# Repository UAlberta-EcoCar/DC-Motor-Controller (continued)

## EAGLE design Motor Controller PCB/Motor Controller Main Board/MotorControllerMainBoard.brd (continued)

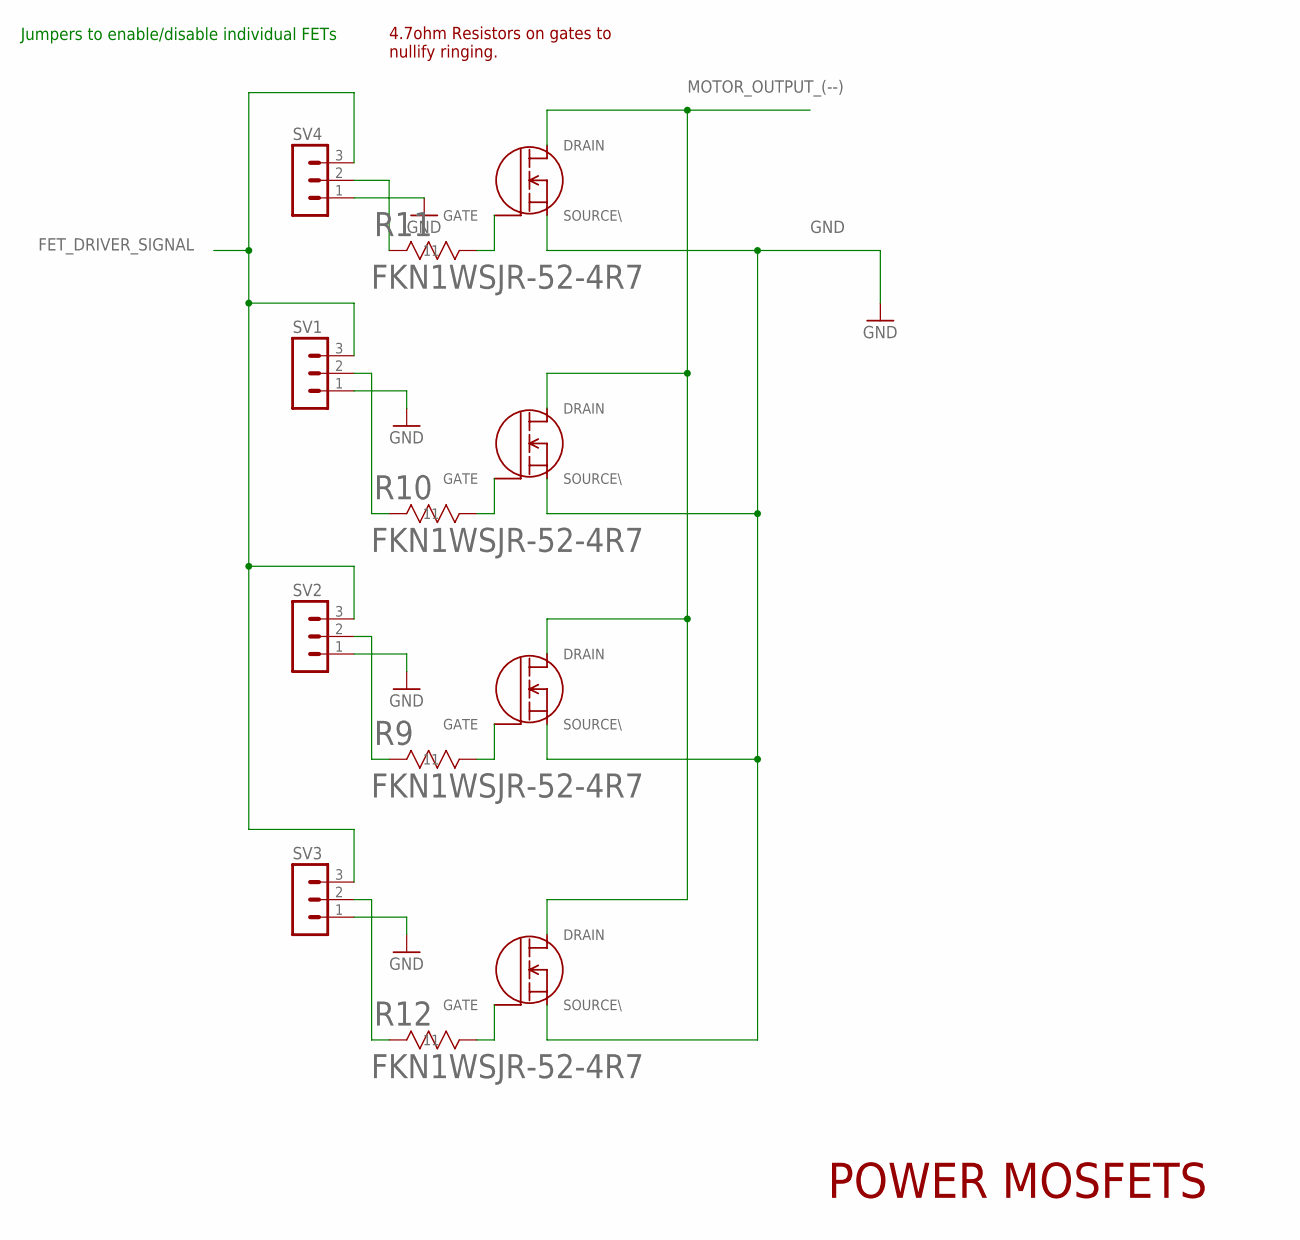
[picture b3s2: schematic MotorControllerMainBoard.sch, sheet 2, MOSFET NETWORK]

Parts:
R9, R10, R11, R12: FKN1WSJR-52-4R7; YAG_FKN50
SV1, SV2, SV3, SV4: MA03-1
U$1, U$2, U$3, U$4: NTMFS5C426NT1G; DNF5

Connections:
FET_DRIVER_SIGNAL: SV1.3, SV2.3, SV3.3, SV4.3; also elsewhere on the board
GND: SV1.1, SV2.1, SV3.1, U$1.SOURCE (SOURCE\), U$2.SOURCE (SOURCE\), U$3.SOURCE (SOURCE\), U$4.SOURCE (SOURCE\); also elsewhere on the board
MOTOR_OUTPUT_(--): U$1.DRAIN, U$2.DRAIN, U$3.DRAIN, U$4.DRAIN; also elsewhere on the board
unnamed: R10.2 (22), U$2.GATE
unnamed: R10.1 (11), SV1.2
unnamed: R12.1 (11), SV3.2
unnamed: R11.1 (11), SV4.2
unnamed: R11.2 (22), U$1.GATE
unnamed: R9.2 (22), U$3.GATE
unnamed: R12.2 (22), U$4.GATE
unnamed: R9.1 (11), SV2.2

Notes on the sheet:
POWER MOSFETS
Jumpers to enable/disable individual FETs
4.7ohm Resistors on gates to nullify ringing.

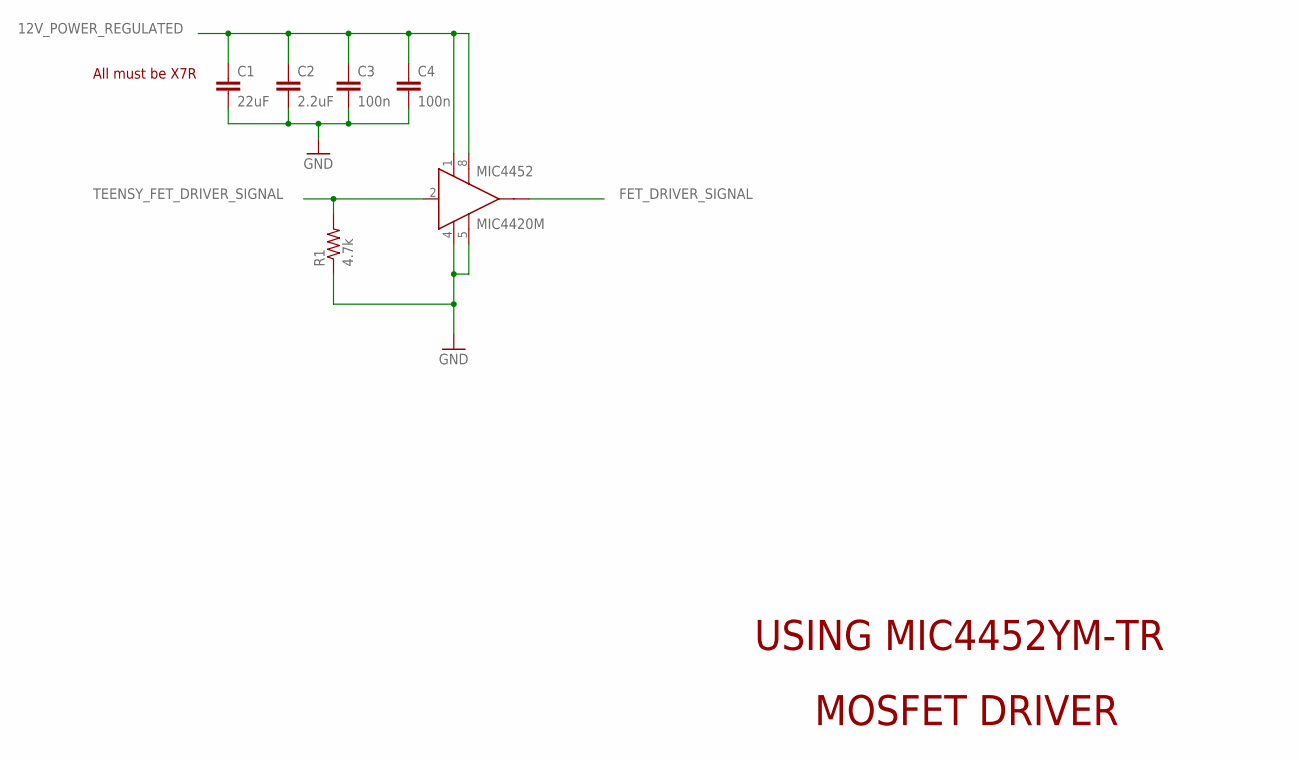
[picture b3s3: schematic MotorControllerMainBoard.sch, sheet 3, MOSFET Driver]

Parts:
C1: 22uF; C1206
C2: 2.2uF; C0805
C3, C4: 100n; C0603
MIC4452: MIC4420M; SO-08
R1: 4.7k; R0805

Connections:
12V_POWER_REGULATED: C1.1, C2.1, C3.1, C4.1, MIC4452.1 (VS), MIC4452.8 (VS1); also elsewhere on the board
FET_DRIVER_SIGNAL: MIC4452.6 (OUT); also elsewhere on the board
GND: C1.2, C2.2, C3.2, C4.2, MIC4452.4 (GND), MIC4452.5 (GND1), R1.1; also elsewhere on the board
TEENSY_FET_DRIVER_SIGNAL: MIC4452.2 (IN), R1.2; also elsewhere on the board

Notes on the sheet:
MOSFET DRIVER
USING MIC4452YM-TR
All must be X7R

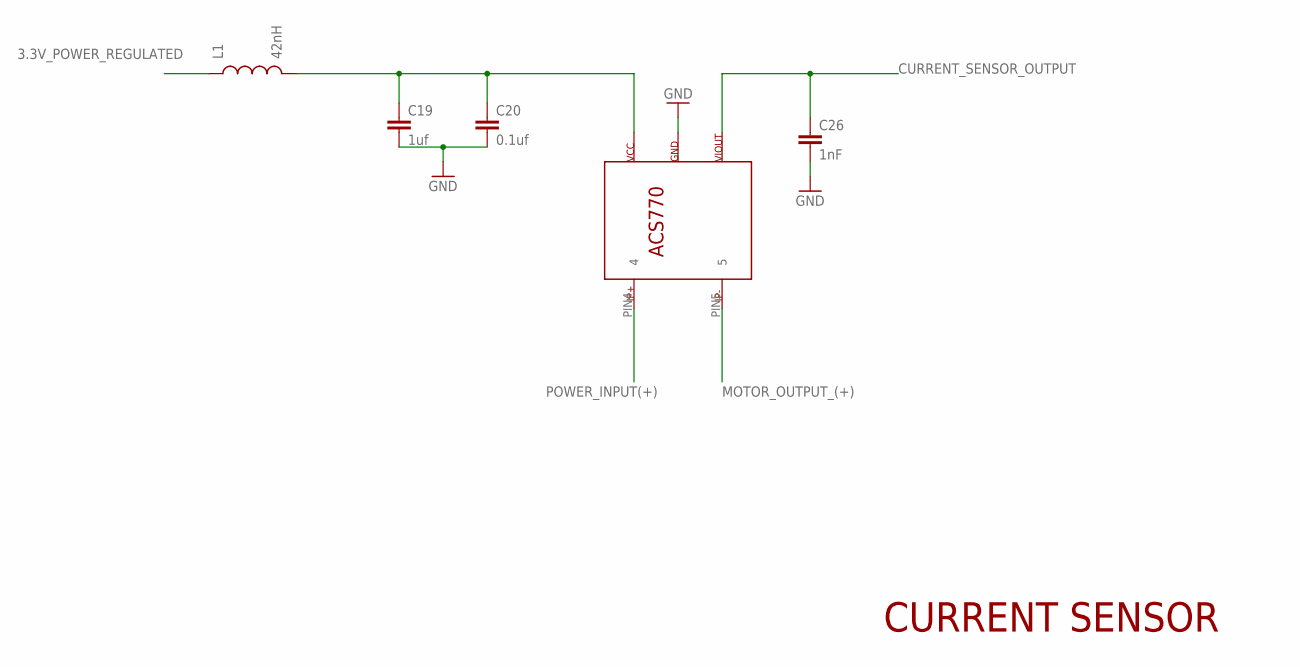
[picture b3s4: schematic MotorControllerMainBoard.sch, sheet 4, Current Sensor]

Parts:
C19: 1uf; C0805
C20: 0.1uf; C0805
C26: 1nF; C0805
L1: 42nH; 0805
U$9: ACS770LCB_CURRENTSENSOR

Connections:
3.3V_POWER_REGULATED: L1.1; also elsewhere on the board
CURRENT_SENSOR_OUTPUT: C26.1, U$9.PIN3 (3); also elsewhere on the board
GND: C19.2, C20.2, C26.2, U$9.PIN2 (2); also elsewhere on the board
MOTOR_OUTPUT_(+): U$9.PIN5 (5); also elsewhere on the board
unnamed: C19.1, C20.1, L1.2, U$9.PIN1 (1)
POWER_INPUT(+): U$9.PIN4 (4)

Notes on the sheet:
CURRENT SENSOR

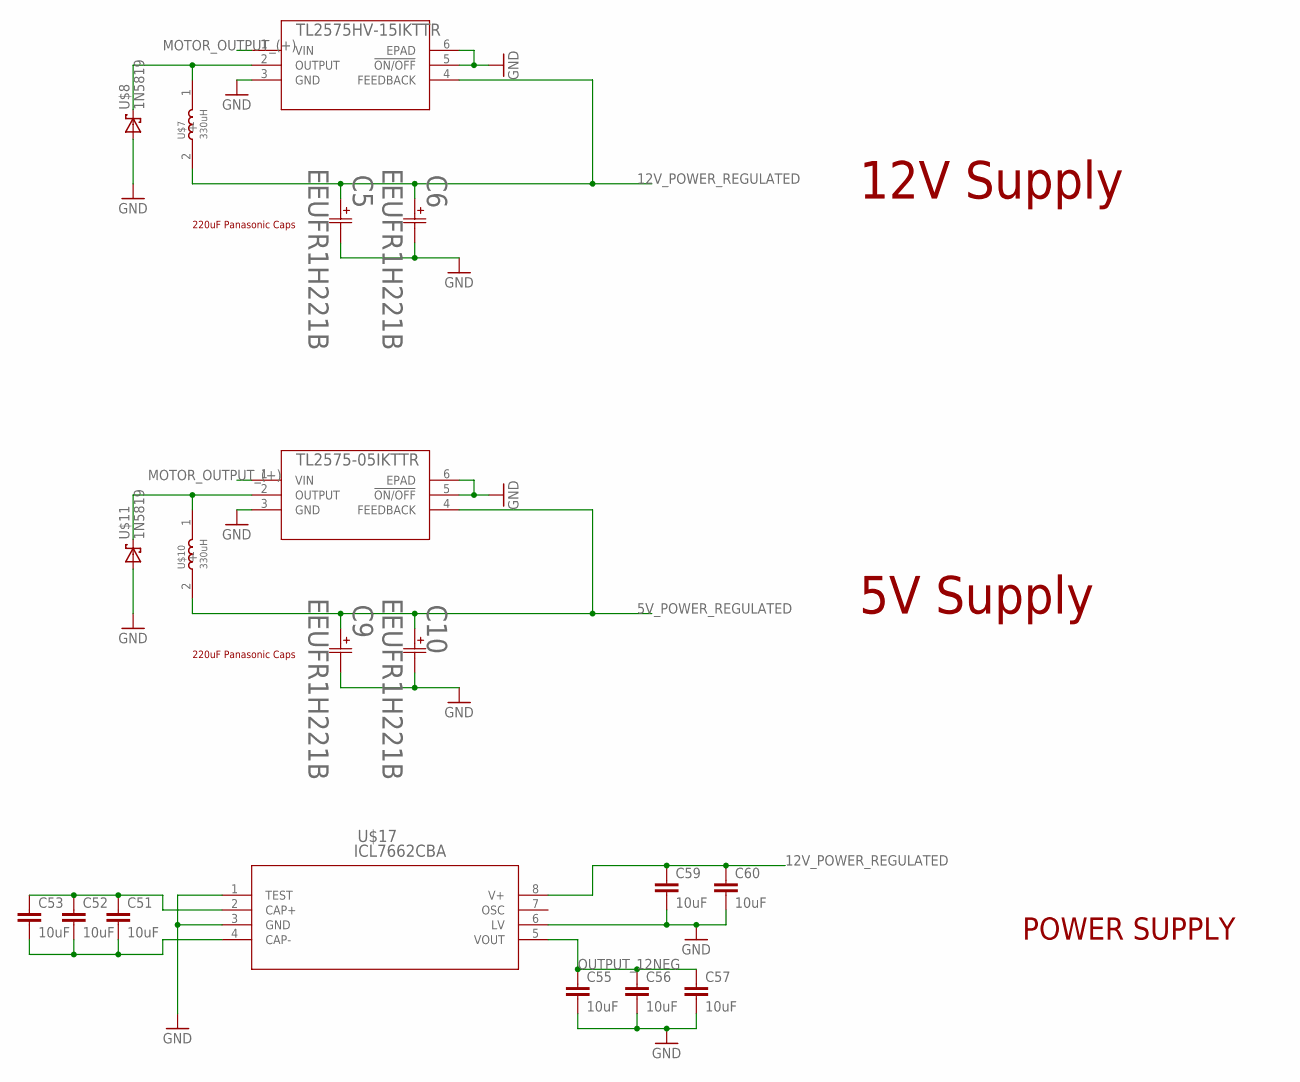
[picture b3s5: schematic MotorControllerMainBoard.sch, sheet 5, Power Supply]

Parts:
C5, C6, C9, C10: EEUFR1H221B; CAP_PAN_10X16
C51, C52, C53, C55, C56, C57, C59, C60: 10uF; C0805
U$6: TL2575HV-15IKTTR; KTT5_6P22X6P86
U$7, U$10: 330uH; INDUCTOR_SMD_FOOTPRINT
U$8, U$11: 1N5819; SOD3715X135N
U$13: TL2575-05IKTTR; KTT5_6P22X6P86
U$17: ICL7662CBA; SO08

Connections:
5V_POWER_REGULATED: C9.1 (11), C10.1 (11), U$10.2 (-), U$13.4 (FEEDBACK); also elsewhere on the board
12V_POWER_REGULATED: C5.1 (11), C6.1 (11), C59.1, C60.1, U$6.4 (FEEDBACK), U$7.2 (-), U$17.8 (V+); also elsewhere on the board
GND: C5.2 (22), C6.2 (22), C9.2 (22), C10.2 (22), C55.2, C56.2, C57.2, C59.2, C60.2, U$6.3 (GND), U$6.5 (!ON/OFF), U$6.6 (EPAD), U$8.A, U$11.A, U$13.3 (GND), U$13.5 (!ON/OFF), U$13.6 (EPAD), U$17.1 (TEST), U$17.3 (GND), U$17.6 (LV); also elsewhere on the board
MOTOR_OUTPUT_(+): U$6.1 (VIN), U$13.1 (VIN); also elsewhere on the board
unnamed: U$6.2 (OUTPUT), U$7.1 (+), U$8.C (K)
unnamed: U$10.1 (+), U$11.C (K), U$13.2 (OUTPUT)
unnamed: C51.1, C52.1, C53.1, U$17.2 (CAP+)
unnamed: C51.2, C52.2, C53.2, U$17.4 (CAP-)
OUTPUT_12NEG: C55.1, C56.1, C57.1, U$17.5 (VOUT); also elsewhere on the board

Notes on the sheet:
POWER SUPPLY
12V Supply
5V Supply
220uF Panasonic Caps

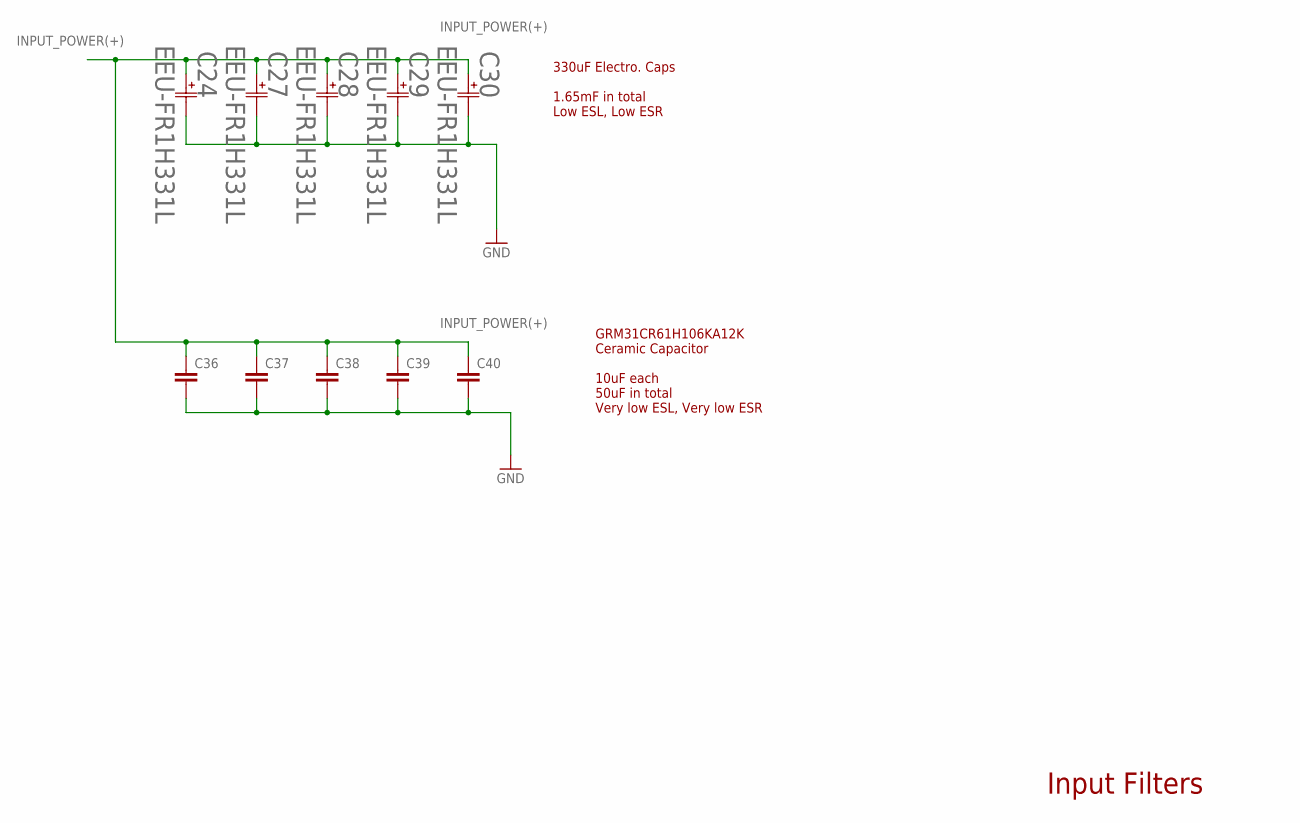
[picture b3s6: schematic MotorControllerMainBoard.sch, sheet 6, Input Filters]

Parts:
C24, C27, C28, C29, C30: EEU-FR1H331L; CAP_EEUFC_10X25
C36, C37, C38, C39, C40: C-EUC1206; C1206

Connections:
GND: C24.2 (22), C27.2 (22), C28.2 (22), C29.2 (22), C30.2 (22), C36.2, C37.2, C38.2, C39.2, C40.2; also elsewhere on the board
INPUT_POWER(+): C24.1 (11), C27.1 (11), C28.1 (11), C29.1 (11), C30.1 (11), C36.1, C37.1, C38.1, C39.1, C40.1; also elsewhere on the board

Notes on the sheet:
Input Filters
GRM31CR61H106KA12K Ceramic Capacitor 10uF each 50uF in total Very low ESL, Very low ESR
330uF Electro. Caps 1.65mF in total Low ESL, Low ESR

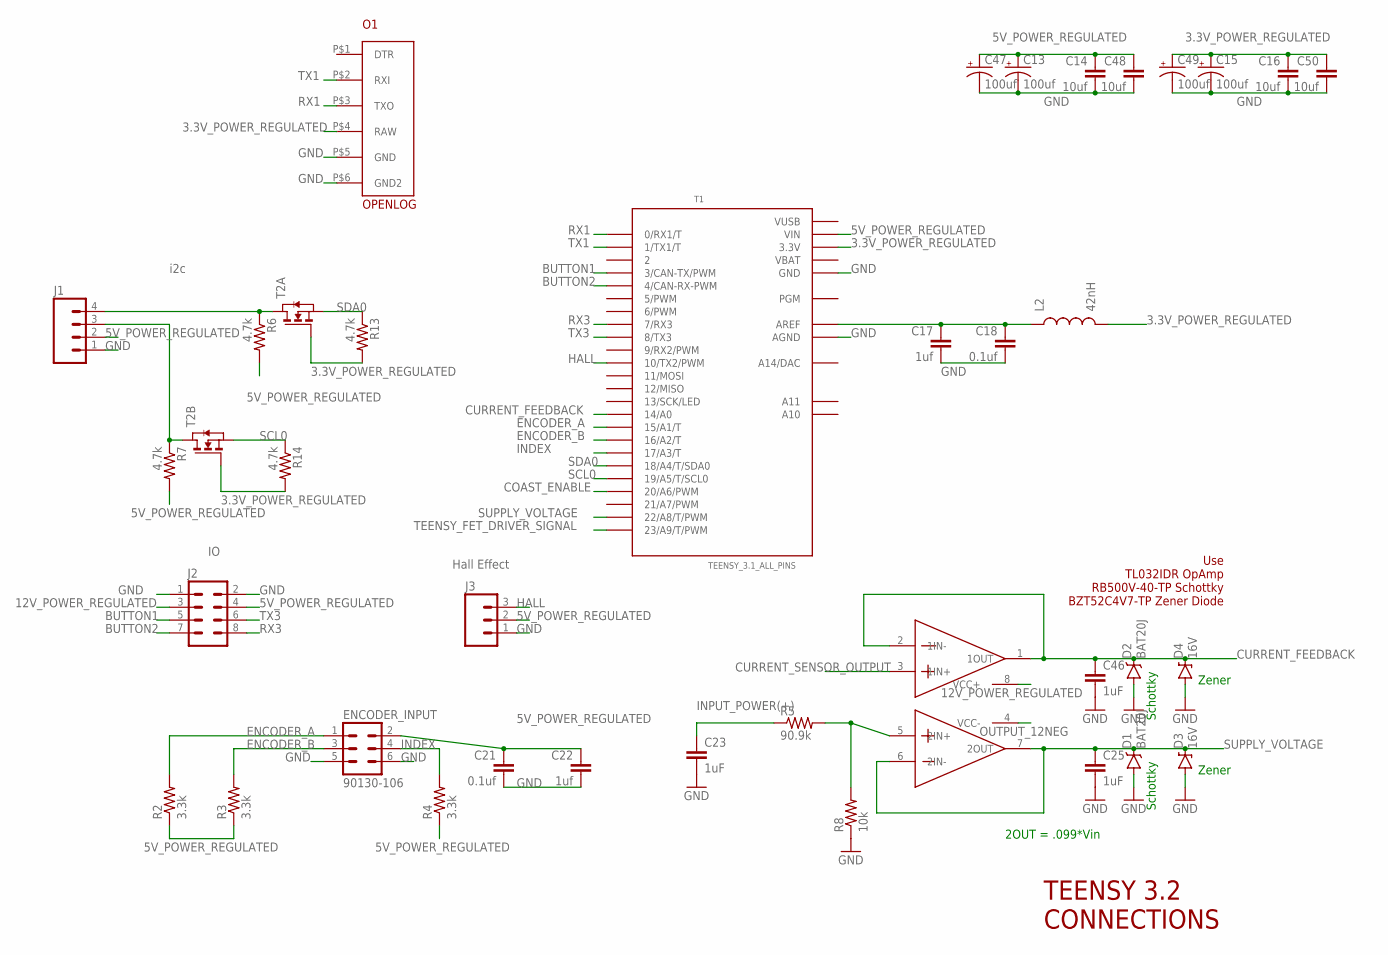
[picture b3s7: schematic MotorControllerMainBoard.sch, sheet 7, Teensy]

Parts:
AD8512ARZ: TL072CDT; D8
C13, C15, C47, C49: 100uf; PANASONIC_C
C14, C16, C48, C50: 10uf; C0805
C17, C22: 1uf; C0805
C18, C21: 0.1uf; C0805
C23, C25, C46: 1uF; C0805
D1, D2: BAT20J; SOD-323
D3, D4: 16V; SOD-123
ENCODER_INPUT: 90130-106; 90130-1?06
J1: M04PTH; 1X04
J2: M04X2; 2X4
J3: M03PTH; 1X03
L2: 42nH; 0805
O1: OPENLOG
R2, R3, R4: 3.3k; R0805
R5: 90.9k; R0805
R6, R7, R13, R14: 4.7k; 0805
R8: 10k; R0805
T1: TEENSY_3.1_ALL_PINS; TEENSY3-ALL_PINS
T2: NMOS2SO8; SO8

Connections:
3.3V_POWER_REGULATED: C15.+, C16.1, C49.+, C50.1, L2.2, O1.P$4 (RAW), R13.2, R14.2, T1.3.3V, T1.3.3V1 (3.3V), T2.2 (G), T2.4 (G); also elsewhere on the board
5V_POWER_REGULATED: C13.+, C14.1, C21.1, C22.1, C47.+, C48.1, ENCODER_INPUT.2, J1.2, J2.4, J3.2, R2.1, R3.1, R4.1, R6.2, R7.2, T1.VIN; also elsewhere on the board
12V_POWER_REGULATED: AD8512ARZ.8 (VCC+), J2.3; also elsewhere on the board
BUTTON1: J2.5, T1.3 (3/CAN-TX/PWM); also elsewhere on the board
BUTTON2: J2.7, T1.4 (4/CAN-RX-PWM); also elsewhere on the board
COAST_ENABLE: T1.20/A6 (20/A6/PWM)
CURRENT_FEEDBACK: AD8512ARZ.1 (1OUT), AD8512ARZ.2 (1IN-), C46.1, D2.C, D4.C, T1.14/A0
CURRENT_SENSOR_OUTPUT: AD8512ARZ.3 (1IN+); also elsewhere on the board
ENCODER_A: ENCODER_INPUT.1, R2.2, T1.15/A1 (15/A1/T)
ENCODER_B: ENCODER_INPUT.3, R3.2, T1.16/A2 (16/A2/T)
GND: C13.-, C14.2, C15.-, C16.2, C17.2, C18.2, C21.2, C22.2, C23.2, C25.2, C46.2, C47.-, C48.2, C49.-, C50.2, D1.A, D2.A, D3.A, D4.A, ENCODER_INPUT.5, ENCODER_INPUT.6, J1.1, J2.1, J2.2, J3.1, O1.P$5 (GND), O1.P$6 (GND2), R8.1, T1.AGND, T1.GND, T1.GND1 (GND); also elsewhere on the board
HALL: J3.3, T1.10 (10/TX2/PWM)
INDEX: ENCODER_INPUT.4, R4.2, T1.17/A3 (17/A3/T)
INPUT_POWER(+): C23.1, R5.1; also elsewhere on the board
unnamed: AD8512ARZ.5 (2IN+), R5.2, R8.2
unnamed: C17.1, C18.1, L2.1, T1.AREF
unnamed: J1.3, R7.1, T2.5 (D), T2.6 (D)
unnamed: J1.4, R6.1, T2.7 (D), T2.8 (D)
OUTPUT_12NEG: AD8512ARZ.4 (VCC-); also elsewhere on the board
RX1: O1.P$3 (TXO), T1.0 (0/RX1/T)
RX3: J2.8, T1.7 (7/RX3)
SCL0: R14.1, T1.19/A5 (19/A5/T/SCL0), T2.3 (S)
SDA0: R13.1, T1.18/A4 (18/A4/T/SDA0), T2.1 (S)
SUPPLY_VOLTAGE: AD8512ARZ.6 (2IN-), AD8512ARZ.7 (2OUT), C25.1, D1.C, D3.C, T1.22/A8 (22/A8/T/PWM)
TEENSY_FET_DRIVER_SIGNAL: T1.23/A9 (23/A9/T/PWM); also elsewhere on the board
TX1: O1.P$2 (RXI), T1.1 (1/TX1/T)
TX3: J2.6, T1.8 (8/TX3)
VBAT: T1.VBAT
VUSB: T1.VUSB

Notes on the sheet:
TEENSY 3.2 CONNECTIONS
2OUT = .099*Vin
Use TL032IDR OpAmp RB500V-40-TP Schottky BZT52C4V7-TP Zener Diode
Zener
Schottky
i2c
Hall Effect

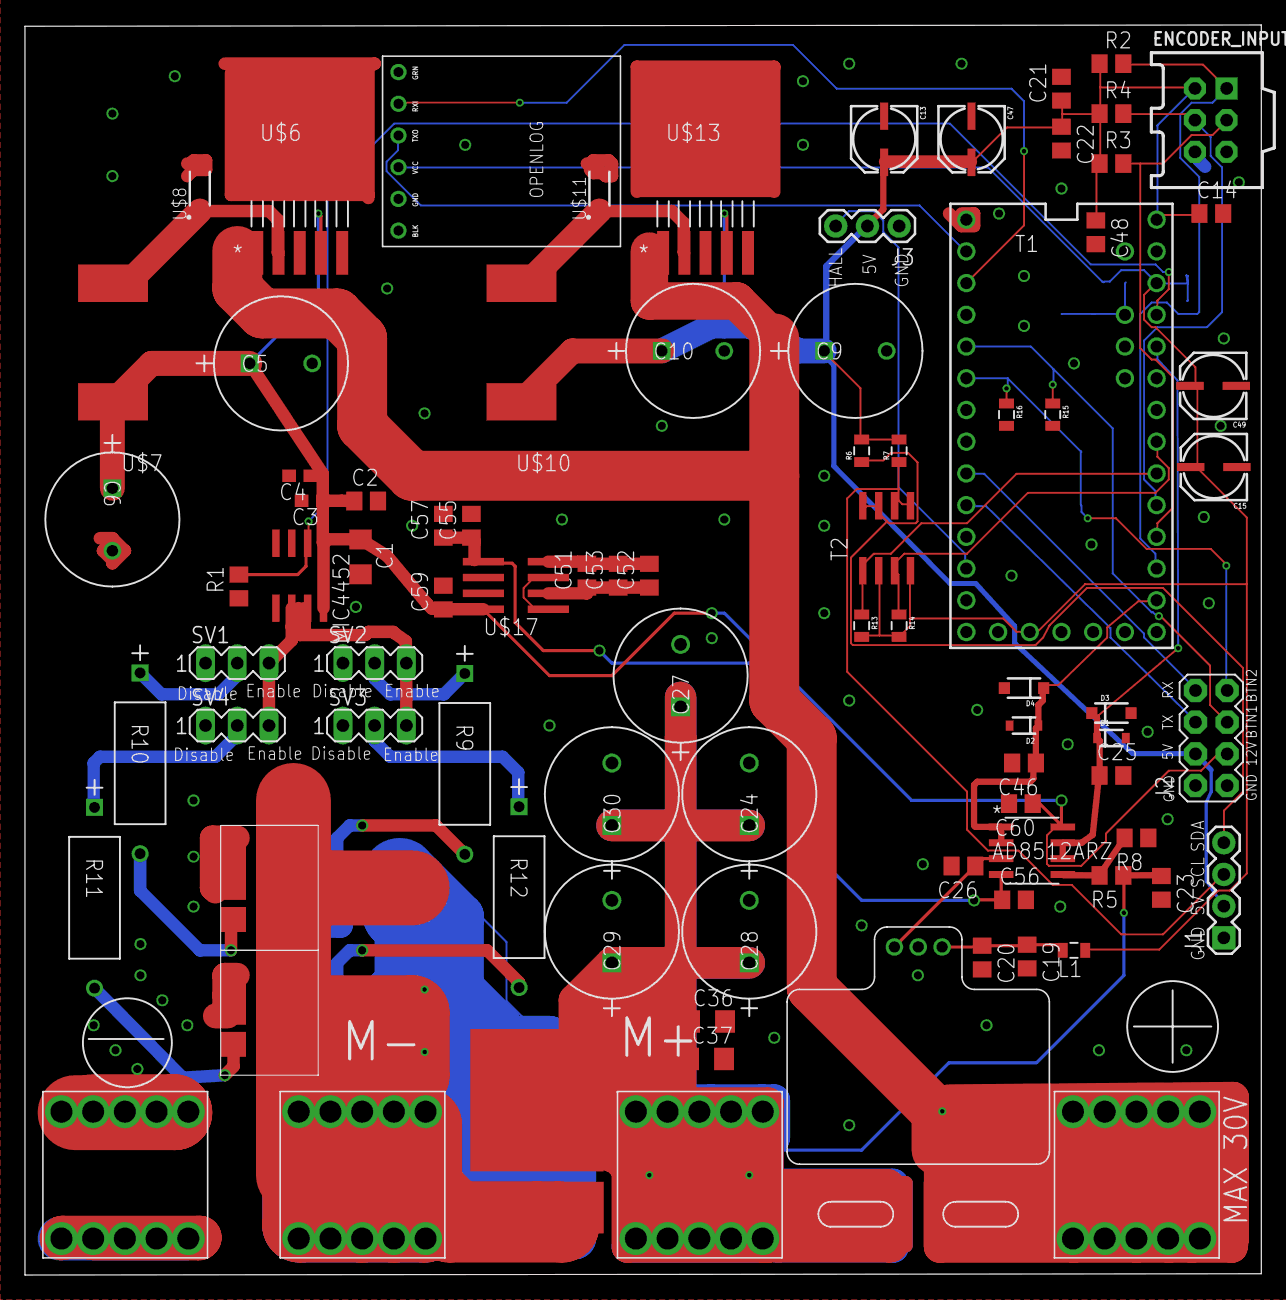
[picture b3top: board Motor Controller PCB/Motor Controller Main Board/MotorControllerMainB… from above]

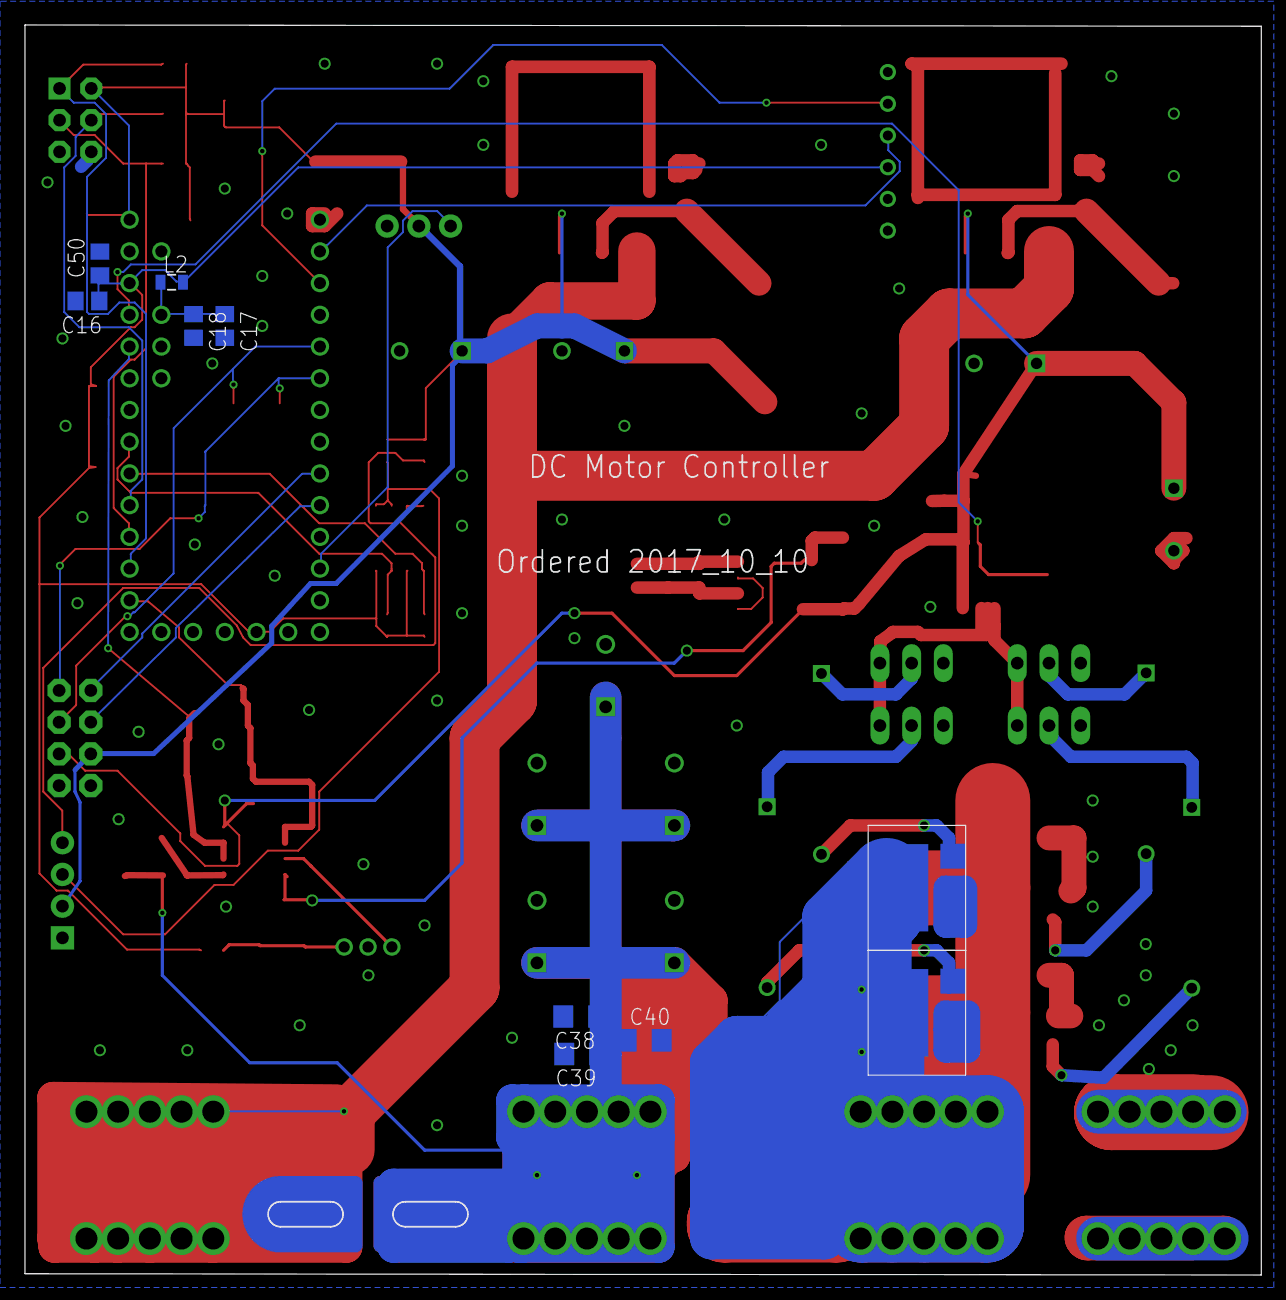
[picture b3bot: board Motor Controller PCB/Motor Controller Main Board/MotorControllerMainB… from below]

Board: 2 copper layers, 98.9 x 100.0 mm, 96 parts (10 on the bottom side), 42 nets.

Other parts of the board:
R15, R16: 10k; 0805

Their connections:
BUTTON1: R15.1; also elsewhere on the board
BUTTON2: R16.1; also elsewhere on the board
GND: R15.2, R16.2; also elsewhere on the board

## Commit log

2017-05-29 Started a general folder layout
    Gotta keep organized !
2017-05-29 Initialized platformIO for atom
2017-06-02 Setup the Topology
    Fill out the boxes! Make use of sheets to keep it simple and tidy.
2017-06-02 Created PID class
    Started working on the PID class
2017-06-03 Added onto PID class
    Continued work on the PID class
2017-06-03 Tested it with a physical setup
    Tested the code with a physical setup, a teensy and a small DC motor. It
    works.
2017-06-06 Added Some Overflow Protections
    Added protections so signed 32 bit integers do not overflow.
2017-06-08 Worked on Overflow Protection
2017-06-09 Added to desision spreadsheet
2017-06-15 Started Simulation
    -Needs some tweaks
    -Needs actual values put into the .m file.
2017-06-15 Added Mosfet Network Block
    Selected a nMOS to use and added it to the eagle schematic.
    Didnt have an eagle part, so I made. I made the pads extra large so we
    can get to it with an iron.
2017-06-16 Added MOSFET Driver
2017-06-19 Replaced code that was lost
2017-06-19 Added Teensy Symbol
2017-06-20 Added Flyback Diode
    Should able to mount the active diode and the schotky diode onto the pad
    layout. Dispite them having different packages.
2017-06-22 Added libraries for the 5V and 15V regulator
2017-06-22 Added datasheet for the 15V and 5V regulator
    They have the same data sheet;
    The TL2575.
2017-06-23 Created Inductor Symbol
2017-06-23 Added Capacitor Library
2017-07-03 Updated Eagle Library
    Updated eagle library, will work on power supply tomorrow
2017-07-04 Worked on 15V and 5V Supply
2017-07-05 Removed Trimpot on Supply
2017-07-06 Modified the mosfet network
    added headers to enable/disable individual fets
    also we're going to drive the fets with 12V instead of 15V.
2017-07-08 Added Teensy Pins
2017-07-14 Changes to current sensor LP filter
2017-07-23 Added buffers
    Choose a JFET op-amp for its ability to reject noise while having high
    input impedance.
    -Used a buffer for the output of the current sensor
    -Used a 1/10 gain buffer to read the voltage of the supply voltage
    safely.
2017-07-25 Decided to use a different op-amp
    A tad more expensive but this new op-amp selection offers little to no
    current or voltage offset voltages.
2017-07-26 Made Several Changes
2017-08-02 Added Current Sensor Part
    Still need to place it on the board (ill probably do it this weekend)
2017-08-02 Implemented the Current Sensor on the Schematic
2017-08-18 Selected a cheaper op-amp
2017-09-05 Added input filter Capacitors.
    3.4mF of input capacitance that has very low effective series resistance
    and inductance.
2017-09-11 Added Screw Terminals to Schematic
    -Added library for the screw terminal
    -Added Power terminals and Motor terminals
2017-09-12 Fixed mistake
    -I put the screw terminal for the negative port for the motor in the
    wrong spot
    -Future update needs resistors on the gates of the FETs. I figure out
    what size of resistor
2017-09-17 Still Working on It
2017-09-19 Added gate resistors
    -4.7ohm on each FET
    -Helps reduce ringing
    -Helps deal with slight difference in capacitance so that they turn on
    closer to at the same time.
2017-09-19 Paralleled power capacitors for the teensy
    -For both the 5V and 3.3V
2017-09-19 Added Negative 12V regulator for op-amps
    -Added a -12V regulator for the op-amps. Low power, simple charge pump
    that inverts the 12V regulator that already exists on the board.
2017-09-23 Preliminary Layout of Large Components
    Layout of large components, will probably move components around. Caps
    look bad and didn't align properly. We can spend time aligning them
    manually once we have the final layout.
2017-09-26 Board work and removed some caps
    -Removed 2 caps from 5V reg and 12V and -12V reg
    -Removed 5 caps from input filter and 5 ceramics
    -Larger components are in place, I started wiring the input caps.
2017-09-27 Placed all components on board
    -They just need wiring.
    -Yes I know it looks sloppy, but we need a quick prototype.
    -Final version of the board will have more thought into component
    placement
2017-09-27 Routed majority of the power components
    -Only thing left is stuff connected to teensy and other things i missed
2017-09-28 Added Header, Worked on Digital Connections
    Added 2x5 header for IO, added 1x3 header for Hall sensor. Worked on
    some digital connections, still a work in progress.
2017-09-29 Revert "Added Header, Worked on Digital Connections"
    This reverts commit b0afa353cafffa68415efb6e73d521797ab7b560.
2017-09-29 Moved teensy over
    -makes wiring easier
    -board is near completion
2017-09-30 Added digital connections
    added digital connects, saving before routing them.
2017-09-30 Moved Some IC's
2017-09-30 Used Autorouter
    Used autorouter (I was tired and wanted to sleep since its 1:30am). It
    looks fine, can fix a few things later.
2017-09-30 Tweaks to traces
    -just did some spot patching.
2017-10-01 Added pin names to silkscreen
    added pin names to silkscreen
2017-10-01 Added labels to the screw terminals
2017-10-01 Added pull down resistors
2017-10-01 Added labels on FET jumpers + minor tweaks to traces
2017-10-07 Revert "Still working on it"
    This reverts commit 5b32f48dc7660ef34d120d46a145852319d558ec.
2017-10-07 DRC tweaks
2017-10-07 DRC Tweaks (3rd times a charm)
2017-10-07 Got rid of the short
2017-10-07 Fixed a couple design rule errors
2017-10-08 made changes to main
    Rewrote most of main.cpp, minor changes to other files as well. Tested
    it with a small motor and seems to be working.
2017-10-10 Gerbers Generated
2017-10-14 Add code for real time monitoring
    For use with i2c 128x64 OLED and a 20x4 i2c liquid crystal.
2017-10-16 Made Historigram a class
    also cleaned up code a little bit
2017-10-19 Just some formating changes
    -restricts the length of the average
2017-10-19 PCB Logic/Power V1.0 (#1)
    * Added Teensy Symbol
    * Added Flyback Diode
    Should able to mount the active diode and the schotky diode onto the pad
    layout. Dispite them having different packages.
    * Added libraries for the 5V and 15V regulator
    * Added datasheet for the 15V and 5V regulator
2017-10-19 Changed the names of the PCB folders to be better represent them
2017-10-22 Added link to gDrive BOM
2017-11-11 Added more comments
2018-01-12 Started Power Board, added optoisolator
    Cleaned up the schematic. Found an optoisolater to replace the original FET driver.
2018-01-15 Added flyback transformer to library
2018-01-15 Minor Touches
2018-01-19 Added opto-isolator amplifier
2018-01-19 Made changes to 12V regulator
2018-01-23 added some leds, removed voltage fb
2018-01-25 Added headers, selected resistor for fet driver
2018-01-26 added heatsink for flyback diode
2018-01-28 Started board work
2018-01-30 Added 5V flyback converter, Teensy
    Added 5V flyback and the Teensy with most of the IO.
2018-02-01 shrunk board size to 10x6cm
2018-02-01 Changed connections to logic board
2018-02-04 this is going to be nuked when i change headers
2018-03-10 Made a layout, need labels
2018-03-12 added TVS diodes and text
2018-03-17 Added via for thermals
2018-03-19 Doing a new layout
2018-03-20 Started routing new layout
    think this is the one bois
2018-03-24 More PCB Progress
    I connected traces together. Hard to explain
2018-03-24 Finishing Touches
